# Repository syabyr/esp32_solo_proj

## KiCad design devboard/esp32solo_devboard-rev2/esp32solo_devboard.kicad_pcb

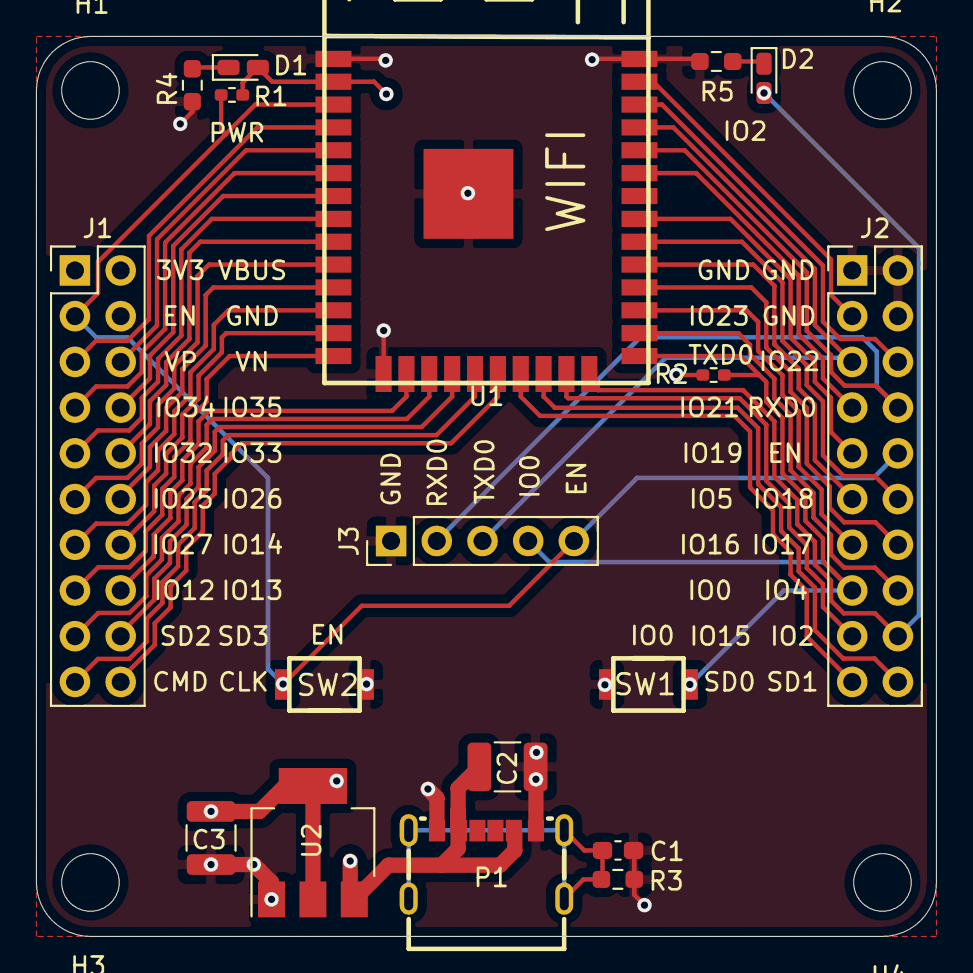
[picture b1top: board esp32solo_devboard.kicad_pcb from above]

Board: 4 copper layers, 50.0 x 50.0 mm, 22 parts (0 on the bottom side), 39 nets.

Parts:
C1: C_Small; C_0603_1608Metric_Pad1.08x0.95mm_HandSolder
C2: C_Small; C_1210_3225Metric_Pad1.33x2.70mm_HandSolder
C3: C_Small; C_1210_3225Metric
D1, D2: LED; LED_0603_1608Metric_Castellated
H1, H2, H3, H4: MountingHole; MountingHole_3.2mm_M3_ISO7380
J1, J2: Conn_02x10_Odd_Even; PinHeader_2x10_P2.54mm_Vertical
J3: Conn_01x05; PinHeader_1x05_P2.54mm_Vertical
P1: USB_C_CHG_6P; USB-C-SMD_TYPEC-250D-BCP6
R1, R2: 10k; R_0402_1005Metric_Pad0.72x0.64mm_HandSolder
R3, R4, R5: 10k; R_0603_1608Metric_Pad0.98x0.95mm_HandSolder
SW1, SW2: SW_Push; turtlekey
U1: ESP32-SOLO-1; WIFIM-SMD_38P-L25.5-W18.0-P1.27
U2: LM1117-3.3; SOT-223-3_TabPin2

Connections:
+3V3: C3.1, D1.2, J1.1, R1.1, R2.1, U1.2, U2.2
CLK: J1.20, U1.20
CMD: J1.19, U1.19
EN: J1.3, J2.10, J3.5, R1.2, SW2.1, U1.3
GND: C1.2, C2.2, C3.2, J1.4, J2.1, J2.2, J2.4, J3.1, P1.A12, P1.B12, R3.2, R4.2, R5.2, SW1.2, SW2.2, U1.1, U1.15, U1.38, U1.39, U2.1
IO0: J2.15, J3.4, R2.2, SW1.1, U1.25
IO2: D2.2, J2.18, U1.24
IO4: J2.16, U1.26
IO5: J2.11, U1.29
IO12: J1.15, U1.14
IO13: J1.16, U1.16
IO14: J1.14, U1.13
IO15: J2.17, U1.23
IO16: J2.13, U1.27
IO17: J2.14, U1.28
IO18: J2.12, U1.30
IO19: J2.9, U1.31
IO21: J2.7, U1.33
IO22: J2.6, U1.36
IO23: J2.3, U1.37
IO25: J1.11, U1.10
IO26: J1.12, U1.11
IO27: J1.13, U1.12
IO32: J1.9, U1.8
IO33: J1.10, U1.9
IO34: J1.7, U1.6
IO35: J1.8, U1.7
unnamed: C1.1, P1.1, P1.2, P1.3, P1.4, R3.1
unnamed: D1.1, R4.1
unnamed: D2.1, R5.1
RXD0: J2.8, J3.2, U1.34
SD0: J2.19, U1.21
SD1: J2.20, U1.22
SD2: J1.17, U1.17
SD3: J1.18, U1.18
SENSOR_VN: J1.6, U1.5
SENSOR_VP: J1.5, U1.4
TXD0: J2.5, J3.3, U1.35
VBUS: C2.1, J1.2, P1.A9, P1.B9, U2.3

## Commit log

2021-09-28 devboard
2021-10-16 3d_case
2021-12-03 rev2
2021-12-03 remove
2022-02-03 proj
